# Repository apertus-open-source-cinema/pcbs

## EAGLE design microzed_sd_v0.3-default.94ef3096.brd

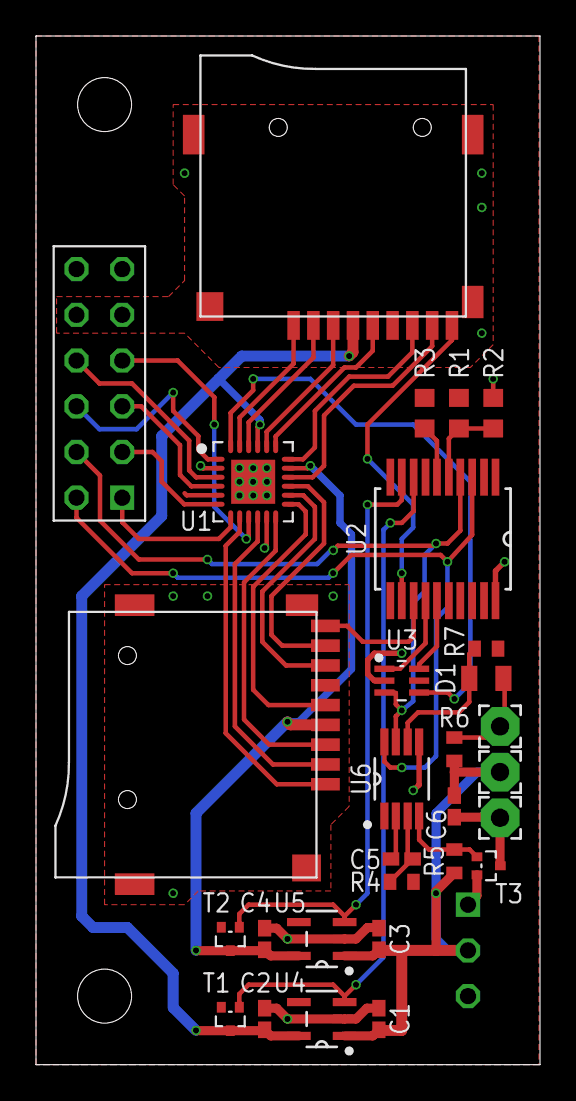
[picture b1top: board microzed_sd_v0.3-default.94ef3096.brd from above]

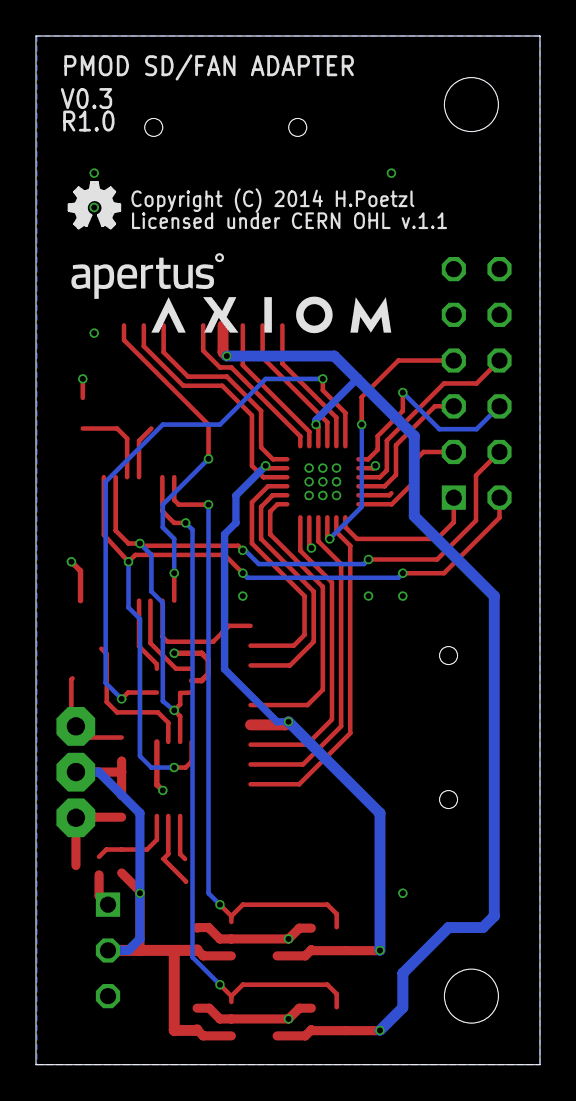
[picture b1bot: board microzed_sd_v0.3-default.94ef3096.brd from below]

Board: 4 copper layers, 28.0 x 57.1 mm, 32 parts (3 on the bottom side), 40 nets.

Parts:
C1, C2, C3, C4, C6: 1µ; C0402K
C5: 2n2; C0402K
D1: MICROMELF-W
LOGO1: OSHW_LOGO_FILLX0100-NT; OSHW_FILLX100_NOTEXT
PAD1, PAD2, PAD3: WIREPAD2,15/1,0; 2,15/1,0
R1, R2: R0603
R3: 10k; R0603
R4: 100R; R0402
R5: 2k2; R0402
R6, R7: 10k; R0402
T1, T2: PMR670UPE; SOT416
T3: PMR290UNE; SOT416
U0: µZ-PMOD-NOHOLES; µZ-TOP-NOHOLES
U1: TXS02612; S-PWQFN-N24
U2: MCP23009-E/SS; SOP65P780X200-20N
U3: 74LVC1G98DW-7; SOT65P210X110-6N
U4, U5: LD6836TD/30P; SOT95P275X110-5N
U6: EMC2101-ACZL; SOP65P490X110-8N
U$1: APERTUS_LOGO334X100; APERTUS_LOGO_334X100
U$13: AXIOM_LOGO525X80; AXIOM_LOGO_525X80
µSD0, µSD1: MICRO-SD3; TF-MICRO-SD_PP3

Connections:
A_CLK: U0.J5-4, U1.9
A_CMD: U0.J5-3, U1.4
A_DAT0: U0.J5-2, U1.6
A_DAT1: U0.J5-1, U1.7
A_DAT2: U0.J5-9, U1.1
A_DAT3: U0.J5-10, U1.3
B0_CLK: U1.19, µSD0.5
B0_CMD: U1.20, µSD0.3
B0_DAT0: U1.18, µSD0.7
B0_DAT1: U1.16, µSD0.8
B0_DAT2: U1.23, µSD0.1
B0_DAT3: U1.22, µSD0.2
B1_CLK: U1.13, µSD1.5
B1_CMD: U1.12, µSD1.3
B1_DAT0: U1.14, µSD1.7
B1_DAT1: U1.15, µSD1.8
B1_DAT2: U1.8, µSD1.1
B1_DAT3: U1.10, µSD1.2
CD0: U2.12, µSD0.CD
CD1: U2.13, µSD1.CD
FAN: C6.2, PAD1.1, T3.3
GND: C1.2, C2.2, C3.2, C4.2, R2.1, T3.2, U0.J5-5, U0.J5-11, U0.JP4-1, U0.JP4-3, U1.2, U1.11, U1.EPAD, U2.20, U3.2, U4.2, U5.2, U6.5, µSD0.6, µSD0.MT1, µSD0.MT2, µSD0.MT3, µSD0.MT4, µSD1.6, µSD1.MT1, µSD1.MT2, µSD1.MT3, µSD1.MT4
unnamed: U2.14, U3.1
unnamed: U2.15, U3.6
unnamed: R1.1, R2.2, U2.5
unnamed: R3.1, U2.6
unnamed: C5.2, U6.2
unnamed: C5.1, R4.1, U6.3
unnamed: R5.2, T3.1, U6.4
unnamed: D1.A, R7.2, U6.6
PWR0: T1.1, U2.8, U4.3
PWR1: T2.1, U2.9, U5.3
SCL: U0.J5-7, U2.3, U6.8
SDA: U0.J5-8, U2.4, U3.3, U6.7
SEL: U1.24, U3.4
TACH: D1.C, PAD3.1, R6.2
VCC: R1.2, R3.2, R7.1, T1.2, T2.2, U0.J5-6, U0.J5-12, U1.5, U2.1, U3.5, U6.1
VCC0: C2.1, T1.3, U1.21, U4.5, µSD0.4
VCC1: C4.1, T2.3, U1.17, U5.5, µSD1.4
VDD: C1.1, C3.1, C6.1, PAD2.1, R5.1, R6.1, U0.JP4-2, U4.1, U5.1

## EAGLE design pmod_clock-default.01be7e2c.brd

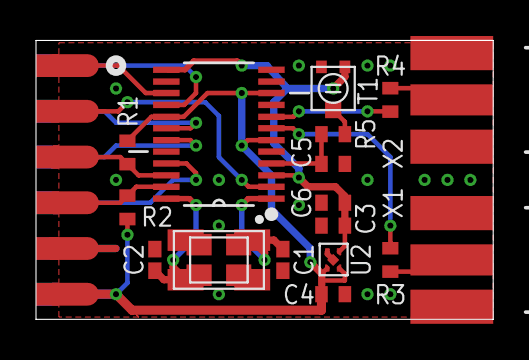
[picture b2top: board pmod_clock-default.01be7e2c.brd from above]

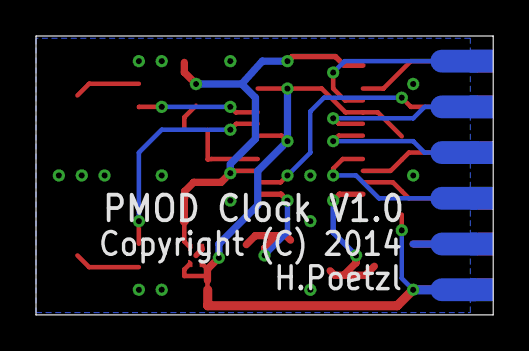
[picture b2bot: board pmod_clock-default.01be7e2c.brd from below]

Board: 2 copper layers, 25.4 x 15.5 mm, 29 parts (6 on the bottom side), 19 nets.

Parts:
C1, C2: 10p; C0402K
C3, C4: 1µ; C0402
C5: 0.1µ; C0402
C6: 100n; C0402
PAD1, PAD2, PAD3, PAD4, PAD5, PAD6, PAD7, PAD8, PAD9, PAD10, PAD11, PAD12: SMD1.27-3.175HR
Q1: SMD-4P-2G5.0X3.2+3.2X2.5; MIX
R1, R2: 4k7; R0402
R3, R4: 22R; R0402
R5: 100k; R0402
T1: PVZ2A; TRIM-PVZ2A
U1: CDCE949PW; SOP65P640X120-24N
U2: LD6805K18H; NXP_LD6805
X1, X2: BU-SMA-E; SMA-EDGE

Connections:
+1V8: C3.1, C6.1, T1.1, U1.3, U1.13, U2.1
+3V3: C4.1, PAD6.1, PAD12.1, R1.2, R2.2, U1.6, U1.10, U1.17, U2.3, U2.4
GND: C1.2, C2.2, C3.2, C4.2, C5.2, C6.2, PAD5.1, PAD11.1, Q1.2, Q1.2@, Q1.4, Q1.4@, T1.3, U1.5, U1.9, U1.14, U1.20, U2.2, U2.5, X1.2@3, X1.2@4, X2.2@3, X2.2@4
unnamed: C1.1, Q1.1, Q1.1@, U1.1
unnamed: C2.1, Q1.3, Q1.3@, U1.24
unnamed: R4.1, X2.1
unnamed: R3.1, X1.1
unnamed: R5.1, T1.2
unnamed: R3.2, U1.7
S0: PAD2.1, U1.2
S1: PAD4.1, R2.1, U1.23
S2: PAD3.1, R1.1, U1.22
VCNTR: C5.1, R5.2, U1.4
Y1: PAD10.1, U1.21
Y2: PAD9.1, U1.19
Y3: PAD8.1, U1.18
Y5: R4.2, U1.8
Y6: PAD7.1, U1.16
Y7: PAD1.1, U1.15

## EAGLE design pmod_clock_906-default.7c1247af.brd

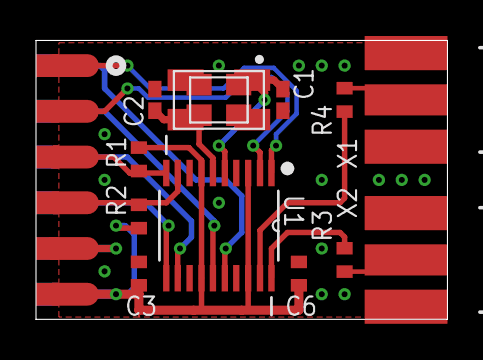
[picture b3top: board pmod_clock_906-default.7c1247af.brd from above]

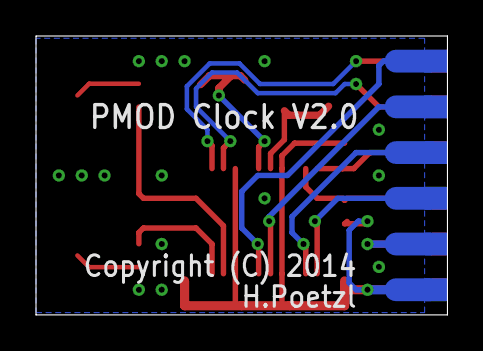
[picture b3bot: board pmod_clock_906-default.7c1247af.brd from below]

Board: 2 copper layers, 22.9 x 15.5 mm, 24 parts (6 on the bottom side), 16 nets.

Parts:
C1, C2: 10p; C0402K
C3: 1µ; C0402
C6: 100n; C0402
PAD1, PAD2, PAD3, PAD4, PAD5, PAD6, PAD7, PAD8, PAD9, PAD10, PAD11, PAD12: SMD1.27-3.175HR
Q1: SMD-4P-2G5.0X3.2+3.2X2.5; MIX
R1, R2: 4k7; R0402
R3, R4: 22R; R0402
U1: CDCE906PW; SOP65P640X120-20N
X1, X2: BU-SMA-E; SMA-EDGE

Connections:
+3V3: C3.1, C6.1, PAD6.1, PAD12.1, R1.2, R2.2, U1.3, U1.7, U1.14, U1.18
GND: C1.2, C2.2, C3.2, C6.2, PAD5.1, PAD11.1, Q1.2, Q1.2@, Q1.4, Q1.4@, U1.4, U1.8, U1.13, U1.17, X1.2@3, X1.2@4, X2.2@3, X2.2@4
unnamed: C1.1, Q1.1, Q1.1@, U1.5
unnamed: C2.1, Q1.3, Q1.3@, U1.6
unnamed: R4.1, X1.1
unnamed: R3.1, X2.1
unnamed: R3.2, U1.20
S0: PAD1.1, U1.1
S1: PAD2.1, U1.2
SCL: PAD3.1, R1.1, U1.10
SDA: PAD4.1, R2.1, U1.9
Y0: PAD10.1, U1.11
Y1: PAD9.1, U1.12
Y2: PAD8.1, U1.15
Y3: PAD7.1, U1.16
Y5: R4.2, U1.19

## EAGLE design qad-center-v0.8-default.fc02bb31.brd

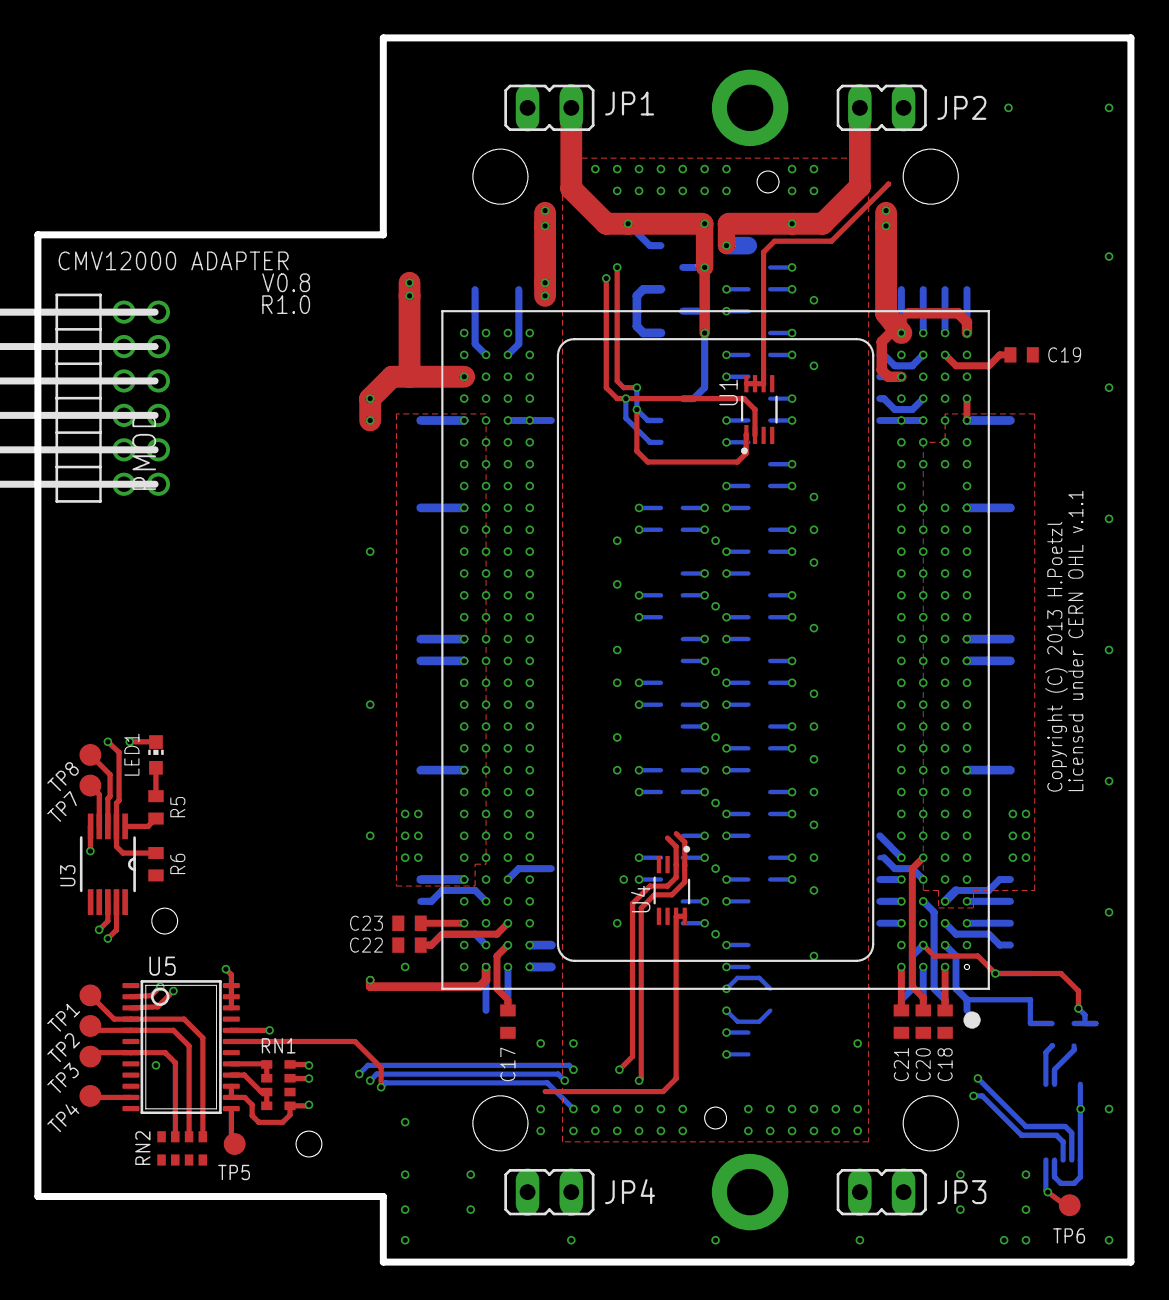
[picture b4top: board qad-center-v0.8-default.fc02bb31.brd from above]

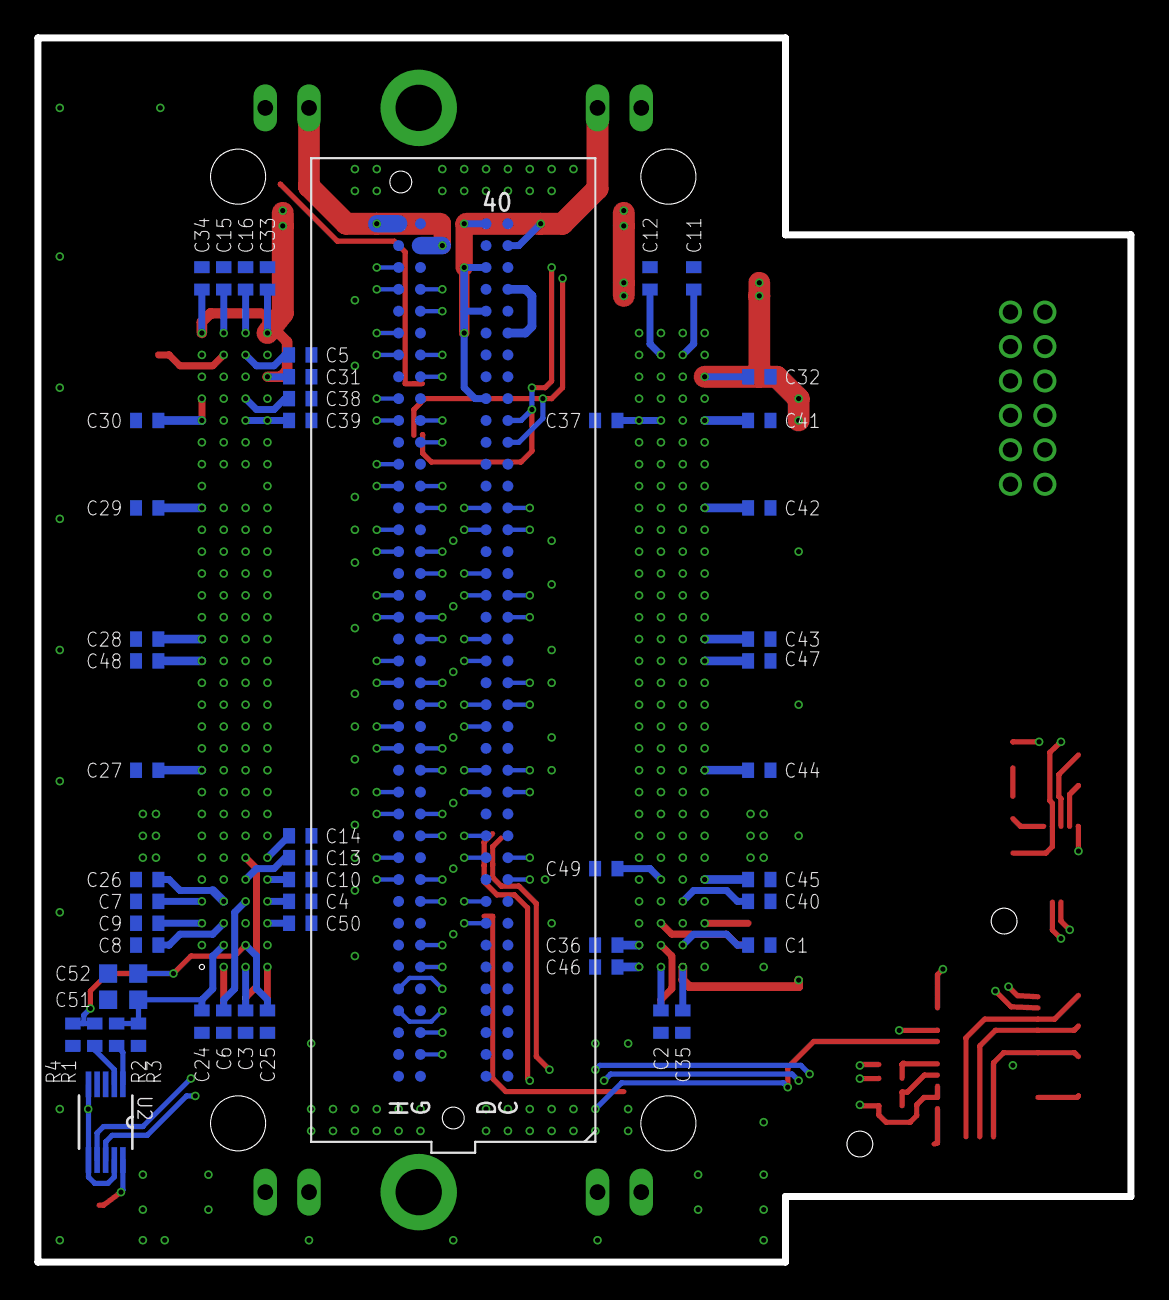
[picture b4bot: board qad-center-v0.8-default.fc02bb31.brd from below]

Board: 4 copper layers, 63.5 x 71.1 mm, 81 parts (50 on the bottom side), 130 nets.

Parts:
C1, C2, C3, C4, C5, C6, C7, C8, C9, C10, C11, C12, C13, C14, C15, C16, C17, C18, C19, C20, C21, C22, C23, C24, C25, C26, C27, C28, C29, C30, C32, C33, C34, C35, C36, C37, C38, C39, C40, C41, C42, C43, C44, C45, C46, C47, C48, C49, C50: C0402
C31: 100n; C0402
C51, C52: C0603K
JP1, JP2, JP3, JP4: JP1
LED1: CHIP-LED0603
PMOD: 87758-1216-PMOD2/90; 2X06/90/2MM
R1, R2, R3, R4, R5, R6: R0402
RN1, RN2: CAT16
TP1, TP2, TP3, TP4, TP5, TP6, TP7, TP8: TPB1,27; B1,27
U1, U4: LM75BGD; SOT996-2/3
U2: AD5647R; SOP50P490X110-10N
U3: PCA9537; TSSOP-10
U5: LM96080; TSSOP24
U$1: CMV12000ANDON+LM; 10-30-07-237-400T4+LM
ZED1: FMC-LPC-ZED_NOCCZED; ASP-134604-01-ZED

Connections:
+1V8: JP2.2, JP3.1, JP4.1
+1V8A: C26.1, C27.1, C28.1, C29.1, C30.1, C48.1, JP3.2, U5.19, U$1.A10, U$1.A15, U$1.A16, U$1.A22, U$1.A26, U$1.A27, U$1.B4
+1V8B: C41.1, C42.1, C43.1, C44.1, C45.1, C46.1, C47.1, JP4.2, U5.20, U$1.E1, U$1.H5, U$1.H10, U$1.H15, U$1.H16, U$1.H22, U$1.H26
+3V0: C31.1, C32.1, C33.1, C34.1, C35.1, RN1.3, U$1.A30, U$1.D28, U$1.D30, U$1.G1, U$1.H28
+3V3: C17.1, C18.1, C19.1, C20.1, C21.1, C22.1, C23.1, C36.1, C37.1, C38.1, C39.1, C40.1, C49.1, C50.1, JP1.2, R6.1, RN1.2, RN2.2, RN2.3, RN2.4, U1.6, U1.7, U1.8, U2.5, U2.6, U2.9, U3.6, U3.10, U4.7, U4.8, U5.1, U5.6, U5.9, U5.12, U$1.C26, U$1.C27, U$1.D3, U$1.D26, U$1.E2, U$1.E26, U$1.F5, U$1.F26, U$1.G4
GND: C1.2, C2.2, C3.2, C4.2, C5.2, C6.2, C7.2, C8.2, C9.2, C10.2, C11.2, C12.2, C13.2, C14.2, C15.2, C16.2, C24.2, C25.2, C26.2, C27.2, C28.2, C29.2, C30.2, C31.2, C32.2, C33.2, C34.2, C35.2, C36.2, C37.2, C38.2, C39.2, C40.2, C41.2, C42.2, C43.2, C44.2, C45.2, C46.2, C47.2, C48.2, C49.2, C50.2, C51.2, C52.2, LED1.C, PMOD.5, PMOD.11, R3.2, R4.2, RN1.1, RN1.4, U1.4, U1.5, U2.3, U2.4, U3.5, U4.4, U4.5, U4.6, U5.8, U5.14, U5.15, U5.18, U5.21, U5.22, U5.23, U5.24, U$1.A9, U$1.A21, U$1.A25, U$1.A28, U$1.A29, U$1.B5, U$1.B22, U$1.B26, U$1.B27, U$1.B28, U$1.C15, U$1.C16, U$1.C28, U$1.D2, U$1.D25, U$1.D27, U$1.D29, U$1.E3, U$1.E15, U$1.E16, U$1.E25, U$1.E27, U$1.F27, U$1.G5, U$1.H1, U$1.H6, U$1.H9, U$1.H21, U$1.H25, U$1.H27, ZED1.C1, ZED1.C4, ZED1.C5, ZED1.C8, ZED1.C9, ZED1.C12, ZED1.C13, ZED1.C16, ZED1.C17, ZED1.C20, ZED1.C21, ZED1.C24, ZED1.C25, ZED1.C28, ZED1.C29, ZED1.C32, ZED1.C33, ZED1.C36, ZED1.C38, ZED1.C40, ZED1.D2, ZED1.D3, ZED1.D6, ZED1.D7, ZED1.D10, ZED1.D13, ZED1.D16, ZED1.D19, ZED1.D22, ZED1.D25, ZED1.D28, ZED1.D37, ZED1.D39, ZED1.G1, ZED1.G4, ZED1.G5, ZED1.G8, ZED1.G11, ZED1.G14, ZED1.G17, ZED1.G20, ZED1.G23, ZED1.G26, ZED1.G29, ZED1.G32, ZED1.G35, ZED1.G38, ZED1.G40, ZED1.H3, ZED1.H6, ZED1.H9, ZED1.H12, ZED1.H15, ZED1.H18, ZED1.H21, ZED1.H24, ZED1.H27, ZED1.H30, ZED1.H33, ZED1.H36, ZED1.H39
unnamed: C17.2, U$1.F2
unnamed: C18.2, U$1.B1
unnamed: C19.2, U$1.B29
unnamed: C20.2, U$1.C6
unnamed: C21.2, U$1.D1
unnamed: C22.2, U$1.F3
unnamed: C23.2, U$1.H3
unnamed: C1.1, U$1.G2
unnamed: C2.1, U$1.F1
unnamed: C3.1, U$1.C1
unnamed: C4.1, U$1.D4
unnamed: C5.1, U$1.C29
unnamed: C6.1, U$1.C4
unnamed: C7.1, U$1.A4
unnamed: C8.1, U$1.B3
unnamed: C9.1, U$1.A3
unnamed: C10.1, U$1.D5
unnamed: C11.1, U$1.G29
unnamed: C12.1, U$1.F29
unnamed: C13.1, U$1.C5
unnamed: C14.1, U$1.D6
unnamed: C15.1, U$1.B30
unnamed: C16.1, U$1.C30
unnamed: U$1.B6, ZED1.H11
unnamed: U$1.B7, ZED1.H10
unnamed: PMOD.1, U$1.F28
unnamed: U$1.D7, ZED1.D12
unnamed: U$1.D8, ZED1.D11
unnamed: PMOD.8, U$1.H29
unnamed: PMOD.2, U$1.E28
unnamed: PMOD.7, U$1.G28
unnamed: PMOD.10, U$1.E30
unnamed: PMOD.4, U$1.G30
unnamed: U$1.B8, ZED1.H14
unnamed: U$1.C9, ZED1.D15
unnamed: U$1.C10, ZED1.D14
unnamed: ZED1.C35, ZED1.C37
unnamed: JP1.1, ZED1.C39, ZED1.D32, ZED1.D36, ZED1.D38, ZED1.D40
unnamed: JP2.1, ZED1.G39, ZED1.H40
unnamed: R1.2, U2.2
unnamed: U$1.G10, ZED1.G13
unnamed: U$1.A11, ZED1.D18
unnamed: U$1.A12, ZED1.D17
unnamed: U$1.C11, ZED1.H17
unnamed: U$1.C12, ZED1.H16
unnamed: U$1.A13, ZED1.D21
unnamed: U$1.A14, ZED1.D20
unnamed: U$1.D13, ZED1.H20
unnamed: U$1.D14, ZED1.H19
unnamed: U$1.F16, ZED1.G22
unnamed: U$1.F17, ZED1.G21
unnamed: U$1.A17, ZED1.H26
unnamed: U$1.A18, ZED1.H25
unnamed: U$1.C17, ZED1.D24
unnamed: U$1.C18, ZED1.D23
unnamed: U$1.A19, ZED1.H29
unnamed: U$1.A20, ZED1.H28
unnamed: U$1.C19, ZED1.D27
unnamed: U$1.C20, ZED1.D26
unnamed: U$1.D21, ZED1.H32
unnamed: U$1.D22, ZED1.H31
unnamed: U$1.A23, ZED1.H35
unnamed: U$1.A24, ZED1.H34
unnamed: U$1.B24, ZED1.H38
unnamed: U$1.B25, ZED1.H37
unnamed: U$1.D15, ZED1.H23
unnamed: U$1.D16, ZED1.H22
unnamed: U$1.G22, ZED1.G34
unnamed: U$1.G23, ZED1.G33
unnamed: U$1.E22, ZED1.G30
unnamed: U$1.E21, ZED1.G31
unnamed: U$1.F21, ZED1.G27
unnamed: U$1.F20, ZED1.G28
unnamed: U$1.E20, ZED1.C26
unnamed: U$1.E19, ZED1.C27
unnamed: U$1.F19, ZED1.G24
unnamed: U$1.F18, ZED1.G25
unnamed: U$1.E18, ZED1.C22
unnamed: U$1.E17, ZED1.C23
unnamed: U$1.H23, ZED1.G37
unnamed: U$1.H24, ZED1.G36
unnamed: U$1.G15, ZED1.G18
unnamed: U$1.G14, ZED1.G19
unnamed: U$1.H14, ZED1.C18
unnamed: U$1.H13, ZED1.C19
unnamed: U$1.G13, ZED1.G15
unnamed: U$1.G12, ZED1.G16
unnamed: U$1.H12, ZED1.C14
unnamed: U$1.H11, ZED1.C15
unnamed: U$1.G11, ZED1.G12
unnamed: U$1.B9, ZED1.H13
unnamed: U$1.F9, ZED1.C10
unnamed: U$1.F8, ZED1.C11
unnamed: U$1.E8, ZED1.G9
unnamed: U$1.E7, ZED1.G10
unnamed: U$1.F7, ZED1.G6
unnamed: U$1.F6, ZED1.G7
unnamed: U$1.E5, ZED1.H5
unnamed: U$1.E6, ZED1.H4
unnamed: U$1.G6, ZED1.G3
unnamed: U$1.G7, ZED1.G2
unnamed: U$1.A5, ZED1.D9
unnamed: U$1.A6, ZED1.D8
unnamed: PMOD.9, U$1.H30
unnamed: PMOD.3, U$1.E29
unnamed: RN2.5, TP1.TP, U5.4
unnamed: PMOD.6, PMOD.12
unnamed: R6.2, U3.2, U$1.F30
unnamed: R5.1, U3.1
unnamed: RN2.6, TP2.TP, U5.5
unnamed: TP8.TP, U3.3
unnamed: TP7.TP, U3.4
unnamed: RN1.5, RN1.6, U5.17
unnamed: RN2.7, TP3.TP, U5.7
unnamed: TP4.TP, U5.11
unnamed: TP5.TP, U5.13
unnamed: RN1.7, RN1.8, U5.16
unnamed: R2.2, U2.1
unnamed: LED1.A, R5.2
unnamed: TP6.TP, U2.10
SCL: U1.2, U2.7, U3.8, U4.2, U5.3, ZED1.C30
SDA: U1.1, U2.8, U3.9, U4.1, U5.2, ZED1.C31
VTREF: C24.1, C51.1, R2.1, R3.1, U$1.B2
VTSIG: C25.1, C52.1, R1.1, R4.1, U$1.C2

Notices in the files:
microzed_sd_v0.3-default.94ef3096.brd:
Copyright (C) 2014 H.Poetzl
Licensed under CERN OHL v.1.1
qad-center-v0.8-default.fc02bb31.brd:
Copyright (C) 2013 H.Poetzl
